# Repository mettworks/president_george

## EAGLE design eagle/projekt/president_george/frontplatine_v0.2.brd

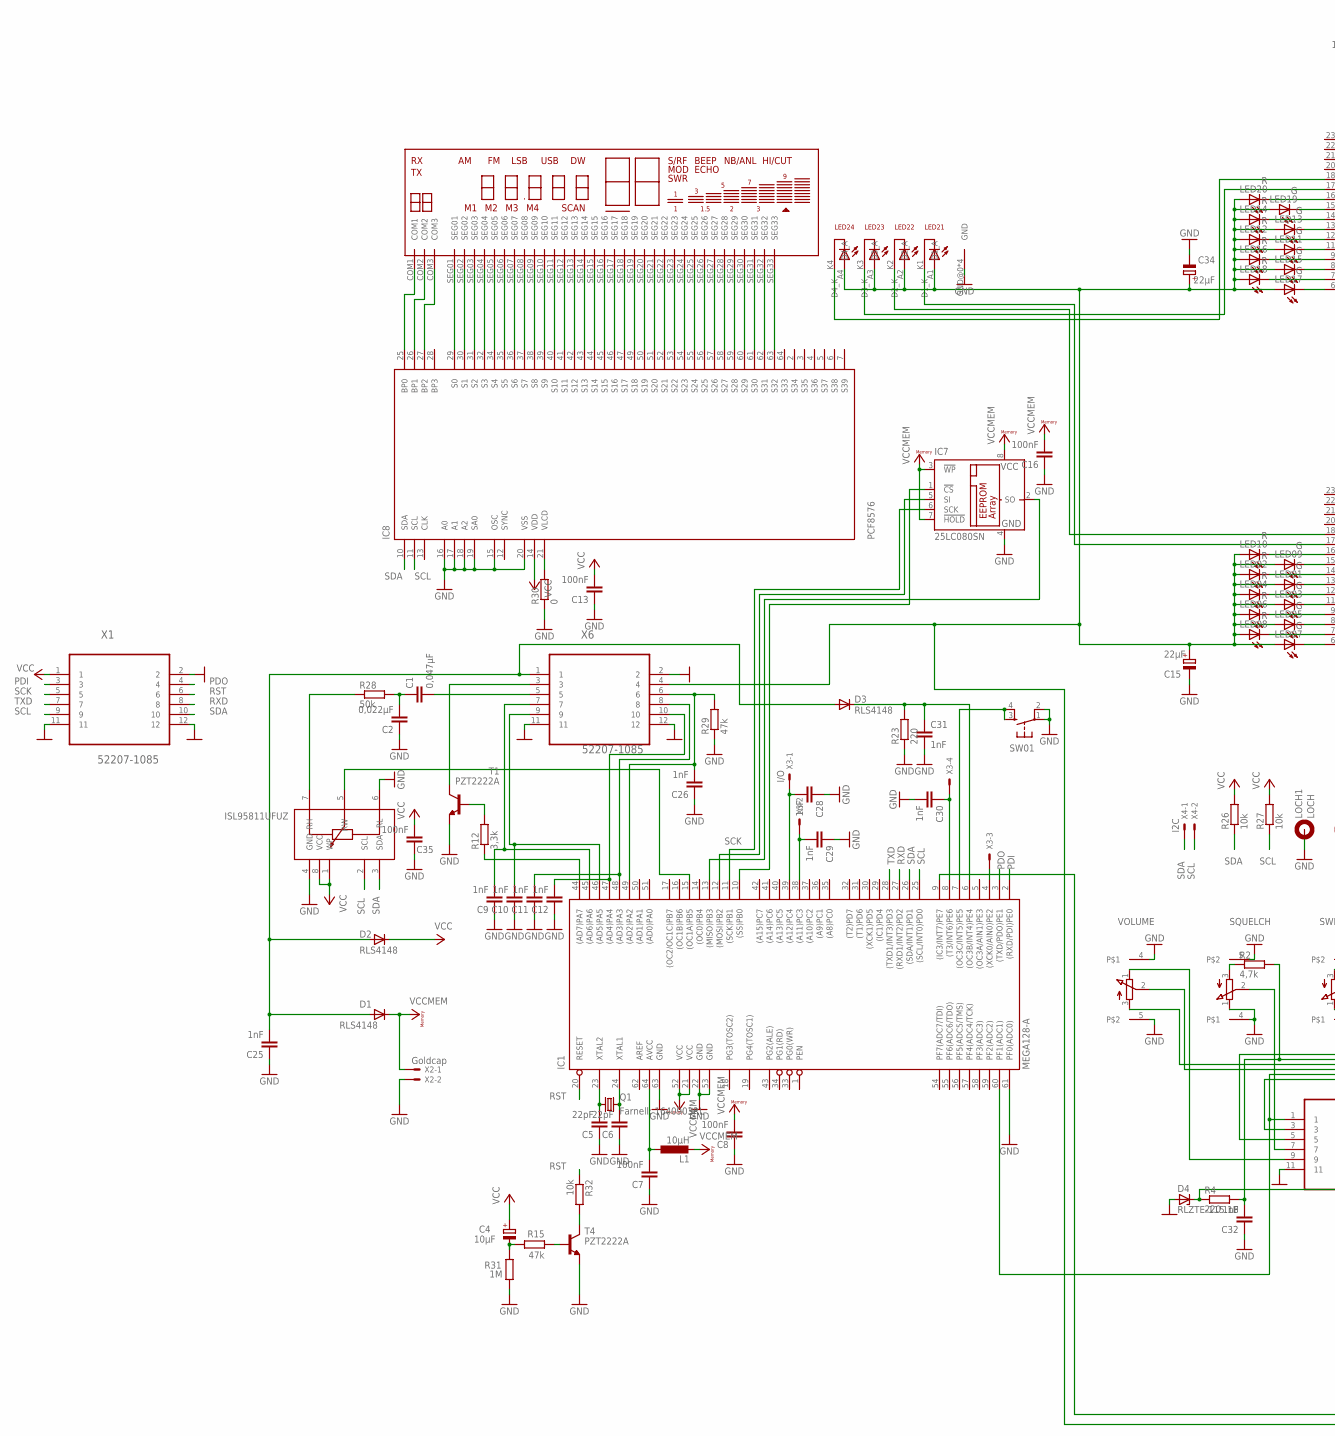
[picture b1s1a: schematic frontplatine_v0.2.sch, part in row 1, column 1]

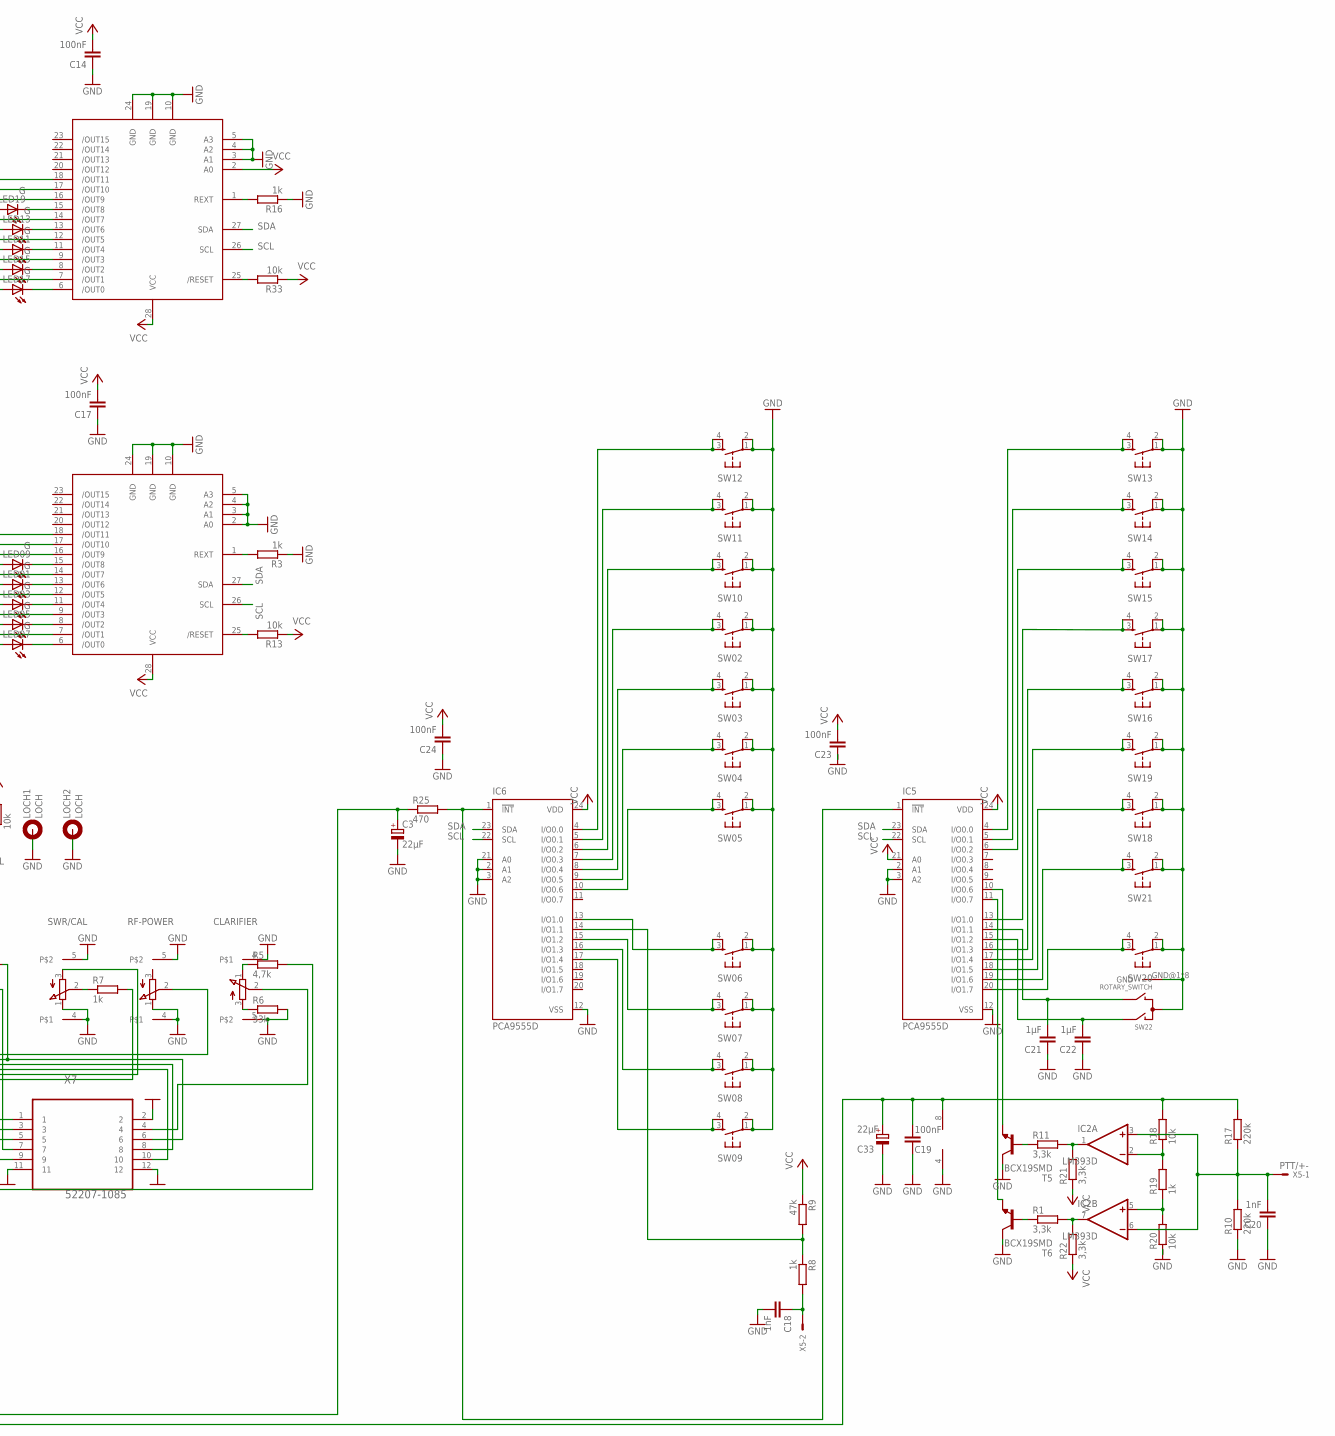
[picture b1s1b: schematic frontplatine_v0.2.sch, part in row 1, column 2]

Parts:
C1: 0,047µF; C1206
C2: 0,022µF; C1206
C3, C15, C33, C34: 22µF; CT3216
C4: 10µF; CT3216
C5, C6: 22pF; C1206
C7, C8, C13, C14, C16, C17, C19, C23, C24, C35: 100nF; C1206
C9, C10, C11, C12, C18, C20, C25, C26, C28, C29, C30, C31, C32: 1nF; C1206
C21, C22: 1µF; C1206
CLARIFIER: POTI
D1, D2, D3: RLS4148; SOD80C
D4: RLZTE-115.1B; SOD80C
DISPLAY1: DISPLAY
IC1: MEGA128-A; TQFP64
IC2: LM393D; SO08
IC3, IC4: TLC59116; TSSOP28
IC5, IC6: PCA9555D; SO24
IC7: 25LC080SN; SO-08; MPN 25LC080/SN
IC8: PCF8576; LQFP-ST-64-2
IC9: ISL95811UFUZ; MSOP8
L1: 10µH; L1812
LED01, LED03, LED05, LED07, LED09, LED11, LED13, LED15, LED17, LED19: G; CHIPLED_1206
LED02, LED04, LED06, LED08, LED10, LED12, LED14, LED16, LED18, LED20: R; CHIPLED_1206
LOCH1, LOCH2: LOCH
Q1: Farnell: 1640903RL; HC49UP
R1, R11, R12, R21, R22: 3,3k; R1206
R2, R5: 4,7k; R1206
R3, R7, R8, R16, R19: 1k; R1206
R4, R23: 220; R1206
R6: 33k; R1206
R9, R15, R29: 47k; R1206
R10, R17: 220k; R1206
R13, R18, R20, R26, R27, R32, R33: 10k; R1206
R25: 470; R1206
R28: 50k; R1206
R30: 0; R1206
R31: 1M; R1206
RF-POWER: POTI
SQUELCH: POTI
SW01, SW02, SW03, SW04, SW05, SW06, SW07, SW08, SW09, SW10, SW11, SW12, SW13, SW14, SW15, SW16, SW17, SW18, SW19, SW20, SW21: TASTER
SW22: ROTARY_SWITCH
SWR/CAL: POTI
T1, T4: PZT2222A; SOT223
T5, T6: BCX19SMD; SOT23-BEC
VOLUME: POTI
X1: 52207-1085; MOLEX_52207-1085
X2: Goldcap; 53047-02
X3: I/O; 53047-04
X4: I2C; 53047-02; MPN 53047-0210
X5: PTT/+-; 53047-02; MPN 53047-0210
X6, X7: 52207-1085; MOLEX_52207-1085; MPN 52207-1085

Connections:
GND: C2.1, C3.-, C5.1, C6.1, C7.1, C8.1, C9.1, C10.1, C11.1, C12.1, C13.1, C14.1, C15.-, C16.1, C17.1, C18.2, C19.1, C20.1, C21.1, C22.1, C23.1, C24.1, C25.1, C26.1, C28.1, C29.1, C30.2, C31.2, C32.1, C33.-, C34.-, C35.1, CLARIFIER.4, CLARIFIER.5, D4.A, DISPLAY1.GND@0 (GND), DISPLAY1.GND@3 (GND), DISPLAY1.GND@6 (GND), DISPLAY1.GND@7 (GND), IC1.22 (GND), IC1.53 (GND), IC1.61 (PF0(ADC0)), IC1.63 (GND), IC2.4 (V-), IC3.2 (A0), IC3.3 (A1), IC3.4 (A2), IC3.5 (A3), IC3.10 (GND), IC3.19 (GND), IC3.24 (GND), IC4.3 (A1), IC4.4 (A2), IC4.5 (A3), IC4.10 (GND), IC4.19 (GND), IC4.24 (GND), IC5.2 (A1), IC5.3 (A2), IC5.12 (VSS), IC6.2 (A1), IC6.3 (A2), IC6.12 (VSS), IC6.21 (A0), IC7.4 (GND), IC8.15 (OSC), IC8.16 (A0), IC8.17 (A1), IC8.18 (A2), IC8.19 (SA0), IC8.20 (VSS), IC9.4 (GND), IC9.6 (RL), LOCH1.B3,0, LOCH2.B3,0, R3.1, R6.2, R10.1, R16.1, R20.1, R23.1, R29.1, R30.1, R31.2, RF-POWER.1 (E), RF-POWER.4, RF-POWER.5, SQUELCH.1 (E), SQUELCH.4, SQUELCH.5, SW01.1, SW01.2, SW02.1, SW02.2, SW03.1, SW03.2, SW04.1, SW04.2, SW05.1, SW05.2, SW06.1, SW06.2, SW07.1, SW07.2, SW08.1, SW08.2, SW09.1, SW09.2, SW10.1, SW10.2, SW11.1, SW11.2, SW12.1, SW12.2, SW13.1, SW13.2, SW14.1, SW14.2, SW15.1, SW15.2, SW16.1, SW16.2, SW17.1, SW17.2, SW18.1, SW18.2, SW19.1, SW19.2, SW20.1, SW20.2, SW21.1, SW21.2, SW22.C, SW22.GND@1 (GND), SW22.GND@2 (GND), SW22.GND@3 (GND), SW22.GND@4 (GND), SW22.GND@5 (GND), SW22.GND@6 (GND), SW22.GND@7 (GND), SW22.GND@8 (GND), SWR/CAL.1 (E), SWR/CAL.4, SWR/CAL.5, T1.3 (E), T4.3 (E), T5.C, T6.C, VOLUME.4, VOLUME.5, X1.2, X1.11, X1.12, X2.2, X6.2, X6.11, X6.12, X7.2, X7.11, X7.12
unnamed: DISPLAY1.SEG01, IC8.29 (S0)
unnamed: VOLUME.2 (S), X7.10
unnamed: VOLUME.1 (E), X7.9
unnamed: VOLUME.3 (A), X7.8
unnamed: D4.C, R4.1, R5.2
unnamed: SQUELCH.2 (S), X7.7
unnamed: R2.1, SQUELCH.3 (A)
unnamed: C32.2, R2.2, R4.2, X7.6
unnamed: CLARIFIER.1 (E), R5.1
unnamed: CLARIFIER.2 (S), X7.4
unnamed: CLARIFIER.3 (A), R6.1
unnamed: IC3.6 (/OUT0), LED07.C
unnamed: R7.2, X7.3
unnamed: R7.1, SWR/CAL.2 (S)
unnamed: DISPLAY1.SEG02, IC8.30 (S1)
unnamed: IC6.14 (I/O1.1), R8.1, R9.2
unnamed: C18.1, R8.2, X5.2
unnamed: IC6.10 (I/O0.6), SW05.3, SW05.4
unnamed: T1.4 (C), X6.3
unnamed: DISPLAY1.SEG03, IC8.31 (S2)
unnamed: DISPLAY1.SEG04, IC8.32 (S3)
unnamed: IC3.7 (/OUT1), LED08.C
unnamed: R12.2, T1.1 (B)
unnamed: C30.1, IC1.8 ((T3/INT6)PE6), X3.4
unnamed: DISPLAY1.SEG05, IC8.34 (S4)
unnamed: C6.2, IC1.24 (XTAL1), Q1.2
unnamed: R32.2, T4.4 (C)
unnamed: DISPLAY1.SEG06, IC8.35 (S5)
unnamed: DISPLAY1.COM1, IC8.25 (BP0)
unnamed: C5.2, IC1.23 (XTAL2), Q1.1
unnamed: IC5.20 (I/O1.7), SW20.3, SW20.4
unnamed: IC3.9 (/OUT3), LED06.C
unnamed: IC3.12 (/OUT5), LED04.C
unnamed: IC3.14 (/OUT7), LED02.C
unnamed: IC3.16 (/OUT9), LED10.C
unnamed: IC4.6 (/OUT0), LED17.C
unnamed: IC3.15 (/OUT8), LED09.C
unnamed: IC3.13 (/OUT6), LED01.C
unnamed: IC3.11 (/OUT4), LED03.C
unnamed: IC3.8 (/OUT2), LED05.C
unnamed: C20.2, IC2.3 (+IN), IC2.6 (-IN), R10.2, R17.1, X5.1
unnamed: IC3.1 (REXT), R3.2
unnamed: IC3.25 (/RESET), R13.2
unnamed: DISPLAY1.COM2, IC8.26 (BP1)
unnamed: IC4.25 (/RESET), R33.2
unnamed: IC4.1 (REXT), R16.2
unnamed: DISPLAY1.COM3, IC8.27 (BP2)
unnamed: IC4.7 (/OUT1), LED18.C
unnamed: C15.+, C19.2, C33.+, C34.+, DISPLAY1.A1 (D1_A), DISPLAY1.A2 (D2_A), DISPLAY1.A3 (D3_A), DISPLAY1.A4 (D4_A), IC2.8 (V+), LED01.A, LED02.A, LED03.A, LED04.A, LED05.A, LED06.A, LED07.A, LED08.A, LED09.A, LED10.A, LED11.A, LED12.A, LED13.A, LED14.A, LED15.A, LED16.A, LED17.A, LED18.A, LED19.A, LED20.A, R17.2, R18.2, X6.4
unnamed: IC4.8 (/OUT2), LED15.C
unnamed: DISPLAY1.SEG07, IC8.36 (S6)
unnamed: DISPLAY1.SEG08, IC8.37 (S7)
unnamed: DISPLAY1.SEG09, IC8.38 (S8)
unnamed: C21.2, IC5.14 (I/O1.1), SW22.B
unnamed: IC1.60 (PF1(ADC1)), SWR/CAL.3 (A), X7.1
unnamed: IC6.9 (I/O0.5), SW04.3, SW04.4
unnamed: IC6.8 (I/O0.4), SW03.3, SW03.4
unnamed: IC6.7 (I/O0.3), SW02.3, SW02.4
unnamed: IC6.6 (I/O0.2), SW10.3, SW10.4
unnamed: IC6.5 (I/O0.1), SW11.3, SW11.4
unnamed: IC6.4 (I/O0.0), SW12.3, SW12.4
unnamed: C22.2, IC5.15 (I/O1.2), SW22.A
unnamed: IC6.15 (I/O1.2), SW07.3, SW07.4
unnamed: IC6.16 (I/O1.3), SW08.3, SW08.4
unnamed: IC6.17 (I/O1.4), SW09.3, SW09.4
unnamed: IC5.4 (I/O0.0), SW13.3, SW13.4
unnamed: IC1.4 ((XCK0/AIN0)PE2), X3.3
unnamed: C28.2, IC1.39 ((A12)PC4), X3.1
unnamed: C29.2, IC1.38 ((A11)PC3), X3.2
unnamed: IC5.19 (I/O1.6), SW21.3, SW21.4
unnamed: IC5.16 (I/O1.3), SW16.3, SW16.4
unnamed: IC5.18 (I/O1.5), SW18.3, SW18.4
unnamed: IC8.21 (VLCD), R30.2
unnamed: IC1.7 ((OC3C/INT5)PE5), SW01.3, SW01.4
unnamed: DISPLAY1.SEG10, IC8.39 (S9)
unnamed: DISPLAY1.SEG11, IC8.40 (S10)
unnamed: DISPLAY1.SEG12, IC8.41 (S11)
unnamed: DISPLAY1.SEG13, IC8.42 (S12)
unnamed: DISPLAY1.SEG14, IC8.43 (S13)
unnamed: DISPLAY1.SEG15, IC8.44 (S14)
unnamed: DISPLAY1.SEG16, IC8.45 (S15)
unnamed: DISPLAY1.SEG17, IC8.46 (S16)
unnamed: DISPLAY1.SEG18, IC8.47 (S17)
unnamed: DISPLAY1.SEG19, IC8.49 (S18)
unnamed: DISPLAY1.SEG20, IC8.50 (S19)
unnamed: DISPLAY1.SEG21, IC8.51 (S20)
unnamed: DISPLAY1.SEG22, IC8.52 (S21)
unnamed: DISPLAY1.SEG23, IC8.53 (S22)
unnamed: DISPLAY1.SEG24, IC8.54 (S23)
unnamed: DISPLAY1.SEG25, IC8.55 (S24)
unnamed: DISPLAY1.SEG26, IC8.56 (S25)
unnamed: DISPLAY1.SEG27, IC8.57 (S26)
unnamed: DISPLAY1.SEG28, IC8.58 (S27)
unnamed: DISPLAY1.SEG29, IC8.59 (S28)
unnamed: DISPLAY1.SEG30, IC8.60 (S29)
unnamed: DISPLAY1.SEG31, IC8.61 (S30)
unnamed: DISPLAY1.SEG32, IC8.62 (S31)
unnamed: DISPLAY1.SEG33, IC8.63 (S32)
unnamed: IC1.44 ((AD7)PA7), R12.1
unnamed: C9.2, IC1.45 ((AD6)PA6), X6.7
unnamed: C10.2, IC1.46 ((AD5)PA5), X6.9
unnamed: C12.2, IC1.47 ((AD4)PA4), X6.10
unnamed: C11.2, IC1.48 ((AD3)PA3), X6.8
unnamed: IC1.15 ((OC1A)PB5), IC9.5 (RW)
unnamed: C26.2, IC1.49 ((AD2)PA2), R29.2, X6.6
unnamed: C3.+, IC1.9 ((IC3/INT7)PE7), R25.1
unnamed: IC4.9 (/OUT3), LED16.C
unnamed: IC1.10 ((SS)PB0), IC7.1 (!CS)
unnamed: IC4.11 (/OUT4), LED11.C
unnamed: C31.1, D3.C, IC1.6 ((OC3B/INT4)PE4), R23.2
unnamed: C25.2, D1.A, D2.A, D3.A, X6.1
unnamed: IC1.13 ((MISO)PB3), IC7.2 (SO)
unnamed: IC1.12 ((MOSI)PB2), IC7.5 (SI)
unnamed: IC2.5 (+IN), R19.1, R20.2
unnamed: IC2.2 (-IN), R18.1, R19.2
unnamed: IC5.17 (I/O1.4), SW19.3, SW19.4
unnamed: IC2.1 (OUT), R11.2, R21.2
unnamed: IC2.7 (OUT), R1.2, R22.2
unnamed: DISPLAY1.K1 (D1_K), IC3.17 (/OUT10)
unnamed: IC5.10 (I/O0.6), T5.E
unnamed: IC5.6 (I/O0.2), SW15.3, SW15.4
unnamed: IC5.11 (I/O0.7), T6.E
unnamed: C1.2, X6.5
unnamed: C1.1, C2.2, R28.2
unnamed: RF-POWER.2 (S), X7.5
unnamed: IC9.7 (RH), R28.1
unnamed: R11.1, T5.B
unnamed: C4.-, R15.2, R31.1
unnamed: R15.1, T4.1 (B)
unnamed: IC6.13 (I/O1.0), SW06.3, SW06.4
unnamed: R1.1, T6.B
unnamed: C7.2, IC1.64 (AVCC), L1.1
unnamed: IC5.5 (I/O0.1), SW14.3, SW14.4
unnamed: IC5.13 (I/O1.0), SW17.3, SW17.4
unnamed: IC5.1 (!INT), IC6.1 (!INT), R25.2
unnamed: IC4.12 (/OUT5), LED12.C
unnamed: IC4.13 (/OUT6), LED13.C
unnamed: IC4.14 (/OUT7), LED14.C
unnamed: IC4.15 (/OUT8), LED19.C
unnamed: IC4.16 (/OUT9), LED20.C
unnamed: DISPLAY1.K2 (D2_K), IC3.18 (/OUT11)
unnamed: DISPLAY1.K3 (D3_K), IC4.17 (/OUT10)
unnamed: DISPLAY1.K4 (D4_K), IC4.18 (/OUT11)
PDI: IC1.2 ((RXD/PDI)PE0), X1.3
PDO: IC1.3 ((TXD/PDO)PE1), X1.4
RST: IC1.20 (RESET), R32.1, X1.6
RXD: IC1.27 ((RXD1/INT2)PD2), X1.8
SCK: IC1.11 ((SCK)PB1), IC7.6 (SCK), X1.5
SCL: IC1.25 ((SCL/INT0)PD0), IC3.26 (SCL), IC4.26 (SCL), IC5.22 (SCL), IC6.22 (SCL), IC8.11 (SCL), IC9.2 (SCL), R27.1, X1.9, X4.2
SDA: IC1.26 ((SDA/INT1)PD1), IC3.27 (SDA), IC4.27 (SDA), IC5.23 (SDA), IC6.23 (SDA), IC8.10 (SDA), IC9.3 (SDA), R26.1, X1.10, X4.1
TXD: IC1.28 ((TXD1/INT3)PD3), X1.7
VCC: C4.+, C13.2, C14.2, C17.2, C23.2, C24.2, C35.2, D2.C, IC3.28 (VCC), IC4.2 (A0), IC4.28 (VCC), IC5.21 (A0), IC5.24 (VDD), IC6.24 (VDD), IC8.14 (VDD), IC9.1 (WP), IC9.8 (VCC), R9.1, R13.1, R21.1, R22.1, R26.2, R27.2, R33.1, X1.1
VCCMEM: C8.2, C16.2, D1.C, IC1.21 (VCC), IC1.52 (VCC), IC7.3 (!WP), IC7.7 (!HOLD), IC7.8 (VCC), L1.2, X2.1

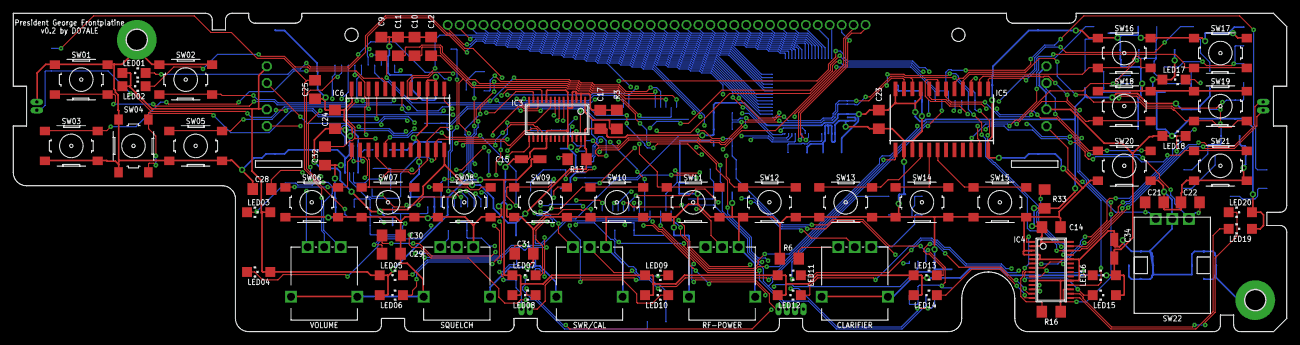
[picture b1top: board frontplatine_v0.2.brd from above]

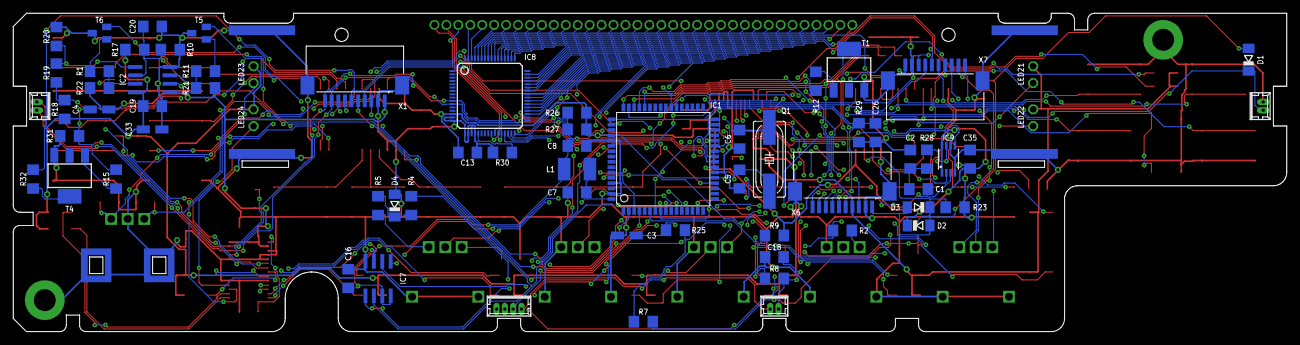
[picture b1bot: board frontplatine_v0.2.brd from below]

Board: 8 copper layers, 192.0 x 48.0 mm, 141 parts (64 on the bottom side), 154 nets.

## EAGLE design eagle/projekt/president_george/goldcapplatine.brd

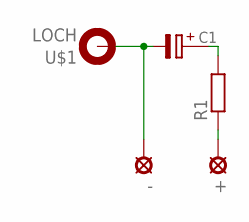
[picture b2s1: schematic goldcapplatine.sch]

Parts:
+: SE11
-: SE11
C1: PAC-21,5; PAC-G-2
R1: R-EU_0207/10; 0207/10
U$1: LOCH

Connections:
unnamed: +.MP, R1.1
unnamed: C1.+, R1.2
unnamed: -.MP, C1.-, U$1.B3,0

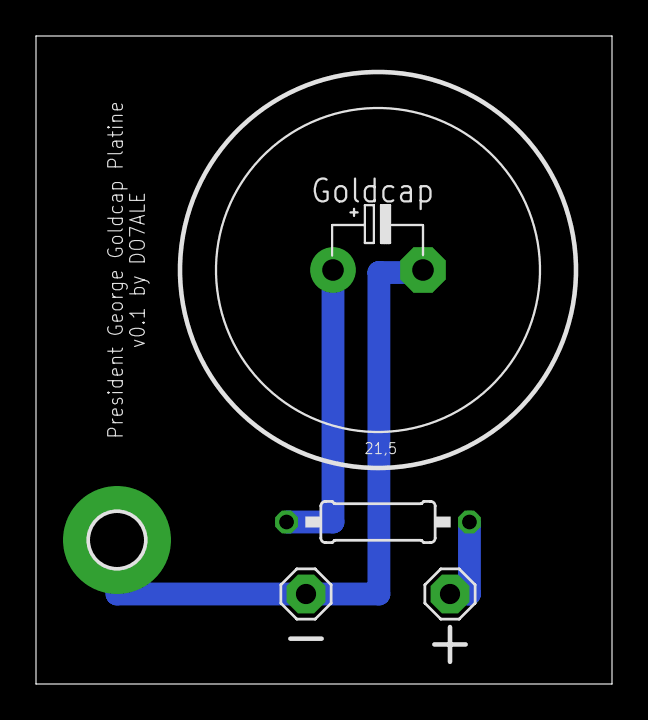
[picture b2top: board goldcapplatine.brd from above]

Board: 8 copper layers, 32.0 x 36.0 mm, 5 parts (0 on the bottom side), 3 nets.

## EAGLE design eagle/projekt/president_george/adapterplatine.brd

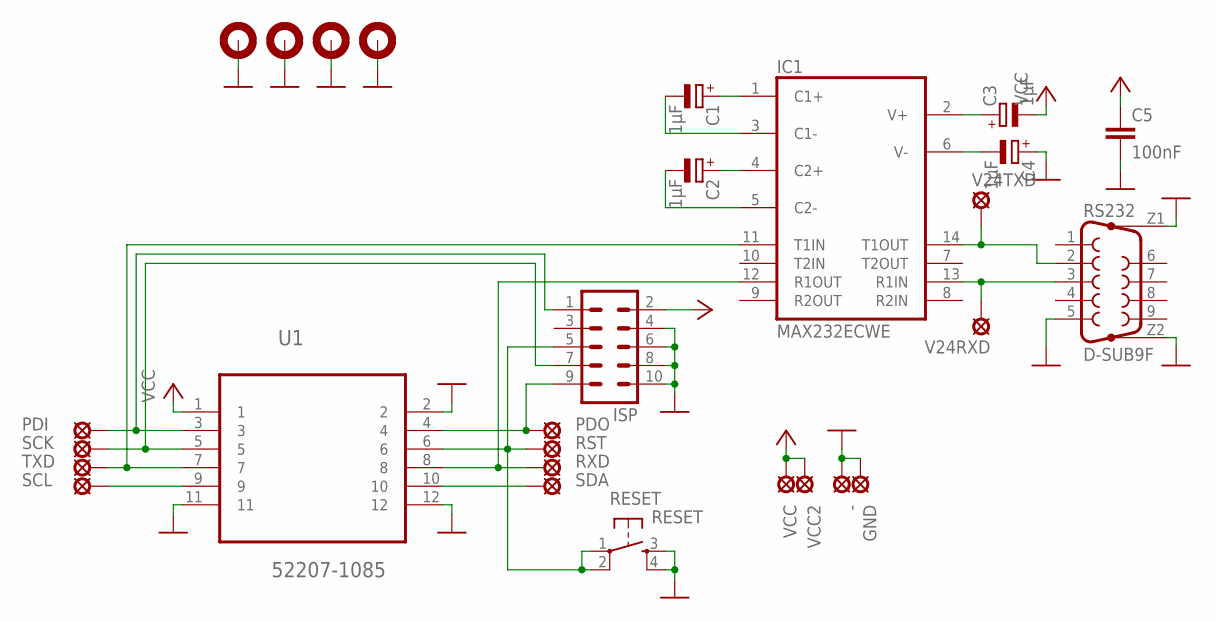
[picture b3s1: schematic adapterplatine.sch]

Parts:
-: SE11
C1, C2, C3, C4: 1µF; CT3216
C5: 100nF; C1206
GND: SE11
IC1: MAX232ECWE; SO16L
ISP: ML10
PDI: SE11
PDO: SE11
RESET: RESET; TASTER
RS232: D-SUB9F
RST: SE11
RXD: SE11
SCK: SE11
SCL: SE11
SDA: SE11
TXD: SE11
U1: 52207-1085; MOLEX_52207-1085
U$1, U$2, U$3, U$4: LOCH
V24RXD, V24TXD: SE11
VCC, VCC2: SE11

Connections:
GND: -.MP, C4.+, C5.2, GND.MP, IC1.15 (GND), ISP.4, ISP.6, ISP.8, ISP.10, RESET.3, RESET.4, RS232.5, RS232.Z1 (G1), RS232.Z2 (G2), U1.2, U1.11, U1.12, U$1.B3,0, U$2.B3,0, U$3.B3,0, U$4.B3,0
unnamed: IC1.14 (T1OUT), RS232.2, V24TXD.MP
unnamed: IC1.13 (R1IN), RS232.3, V24RXD.MP
unnamed: C1.+, IC1.1 (C1+)
unnamed: C1.-, IC1.3 (C1-)
unnamed: C2.+, IC1.4 (C2+)
unnamed: C2.-, IC1.5 (C2-)
unnamed: C4.-, IC1.6 (V-)
unnamed: C3.+, IC1.2 (V+)
unnamed: IC1.11 (T1IN), TXD.MP, U1.7
unnamed: IC1.12 (R1OUT), RXD.MP, U1.8
unnamed: ISP.1, PDI.MP, U1.3
unnamed: ISP.5, RESET.1, RESET.2, RST.MP, U1.6
unnamed: ISP.7, SCK.MP, U1.5
unnamed: ISP.9, PDO.MP, U1.4
unnamed: SCL.MP, U1.9
unnamed: SDA.MP, U1.10
VCC: C3.-, C5.1, IC1.16 (VCC), ISP.2, U1.1, VCC.MP, VCC2.MP

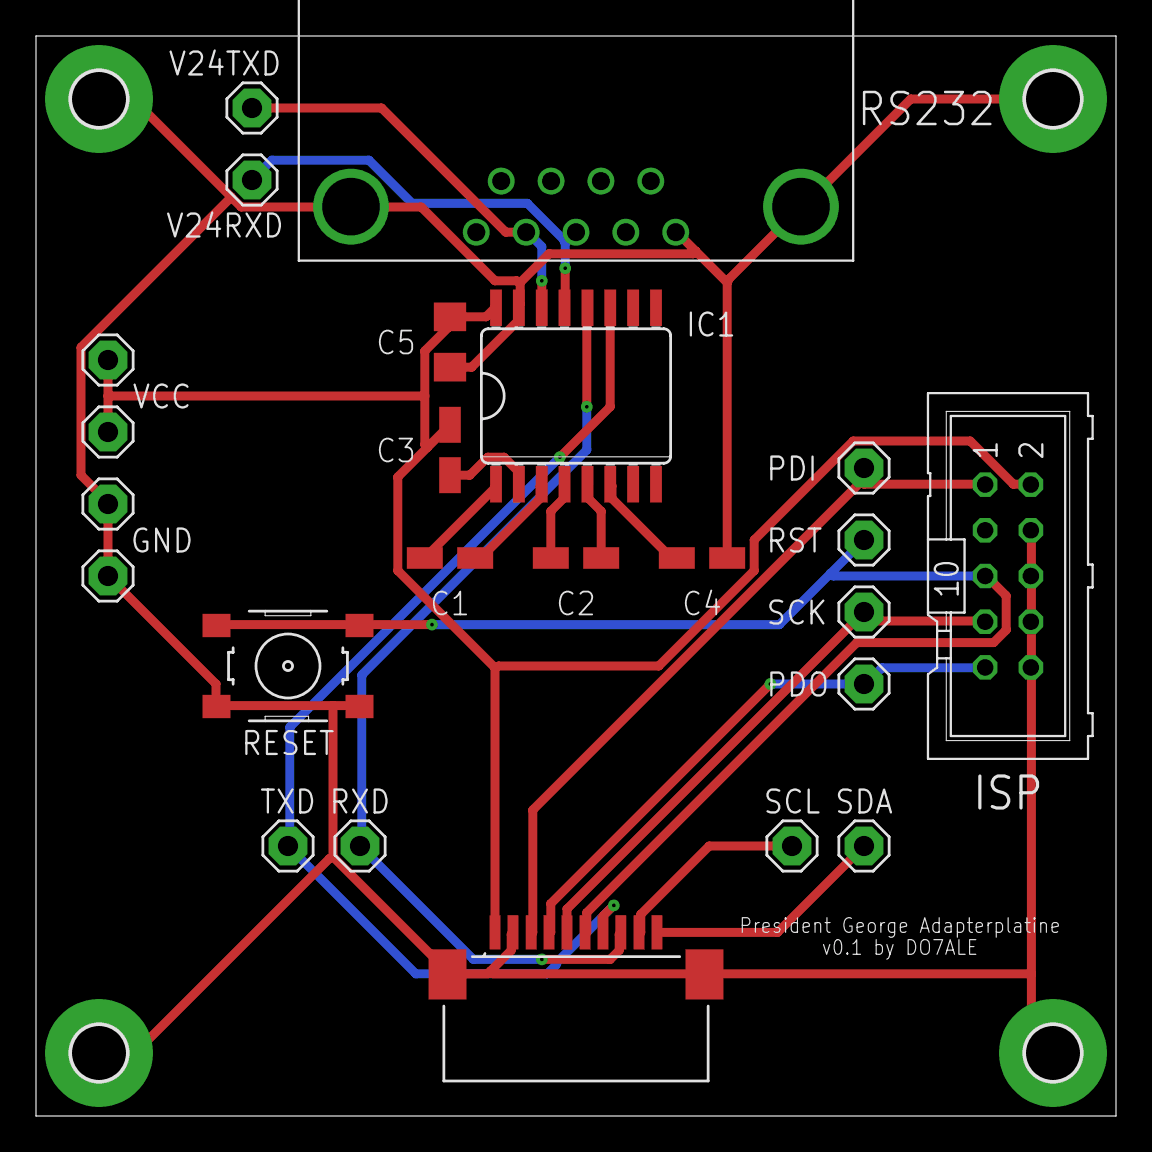
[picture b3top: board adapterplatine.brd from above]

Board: 8 copper layers, 60.0 x 60.0 mm, 28 parts (0 on the bottom side), 18 nets.

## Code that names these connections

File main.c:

/*
avrdude -p atmega128 -P /dev/ttyACM0 -c stk500v2 -v -Uefuse:w:0xFF:m -U hfuse:w:0xC9:m -U lfuse:w:0xDF:m
*/

#include <avr/io.h>
#include <util/delay.h>
#include <avr/interrupt.h>
#include "memory.h"
#include "display.h"
#include "led.h"
#include "transceiver.h"
#include "operating.h"
#include "i2c.h"
#ifdef debug
#include "debug.h"
#include <stdlib.h>
#include <stdio.h>
#include <stdint.h>
#endif

int ichbinaus=0;
int led_farbe=0;
unsigned int led_dimm1=128;
unsigned int led_dimm2=128;
unsigned int memory[MEM_SIZE];
int mod;
//unsigned int freq = 28225;
unsigned int freq;
unsigned int cb_channel;
unsigned int cb_mod;
unsigned int step = 5;
int txstat=0;

int modus;

//
// Counter für S-Meter
unsigned int adccounter=20;
unsigned int adcvalues[20];
#define ADCMESSUNGEN 20;



//
// IRQ für Spannungsabfall
// wegspeichern der Einstellungen im EEPROM
// beim wiederkommen von VCC, wird durch ein RC Glied Reset ausgelöst
ISR (INT4_vect)
{
	#ifdef debug
	uart_puts("INT4_vect()\r\n");
	#endif
	off();
}

ISR (INT5_vect)
{
	#ifdef debug
	uart_puts("INT5_vect()\r\n");
	#endif
	if(ichbinaus == 1)
	{
		#ifdef debug
		uart_puts("AN\r\n");
		#endif
	  PORTA |= (1<<PA7);	// einschalten
		led_pwm(1,0);
		led_pwm(2,0);
		led_pwm(3,0);
		led_pwm(4,0);
		led_pwm(5,0);
		led_pwm(6,0);
		led_pwm(7,0);
		led_pwm(8,0);
		led_pwm(9,0);
		led_pwm(10,0);
		led_pwm(11,0);
		led_pwm(12,0);
		init_geraet();
		ichbinaus=0;
	}
	else
	{
		ichbinaus=1;
		#ifdef debug
		uart_puts("AUS\r\n");
		#endif
		save2memory();
		PORTA &= ~(1<<PA7);	// ausschalten...
		led_pwm(1,0);
		led_pwm(2,0);
		led_pwm(3,0);
		led_pwm(4,0);
		led_pwm(5,0);
		led_pwm(6,0);
		led_pwm(7,0);
		led_pwm(8,0);
		led_pwm(9,0);
		led_pwm(10,0);
		led_pwm(11,0);
		led_pwm(12,0);
	}
}

ISR (INT7_vect)
{
	
	#ifdef debug
	uart_puts("INT7\r\n");
	#endif
	
	keycheck();
}



ISR(BADISR_vect)
{
	#ifdef debug
  uart_puts("RESET AUSGELOEST!\r\n");
	uart_puts("nicht definierter Interrupt!\r\n");
	uart_puts("STOP\r\n");
	#endif
	while(1)
	{
	}
}
/*
//
// sehr unelegant, muss mit einem Timer gemacht werden
// erstmal geht es nur um den HW Test ... ^^
void scan(void)
{
	while(1)
	{
		freq=freq+step;
		tune(freq,step);
		_delay_ms(250);
		if ( !(PINA & (1<<PINA2)) )
		{
			#ifdef debug
			uart_puts("Treffer\r\n");
			#endif
			break;
		}
	}
}
*/

uint16_t adc_read(void )
{
	// ADC1 auswählen
	//ADMUX |= (1<<MUX0);
	//ADMUX |= (1 << MUX3) | (1<<MUX0);
	ADMUX |= (1<<MUX0);

  ADCSRA |= (1<<ADSC);
  while (ADCSRA & (1<<ADSC) ) 
	{   
  }
  return ADCW;                   
}

void messung_s(void)
{
	uint16_t messwert;
	messwert=adc_read();
	uint32_t sum=0;
	unsigned int i;
	//char s[7];

	
	if(adccounter == 0)
	{
		i=ADCMESSUNGEN;
		while(i > 0)
		{
			sum=sum+adcvalues[i];
			i--;
		}
		sum=sum/ADCMESSUNGEN;
		/*
		uart_puts("Durchschnitt: ");
		uart_puts( itoa( sum, s, 10 ) );
		uart_puts("\r\n");
		*/
		display_write_meter(sum);
		adccounter=ADCMESSUNGEN;
	}
	else
	{
		adcvalues[adccounter]=messwert;
		adccounter--;
	}
}


void adc_init(void)
{
	ADCSRA |= (1 << ADPS2) | (1 << ADPS1) | (1 << ADPS0); // Set ADC prescaler to 128 - 125KHz sample rate @ 16MHz
	ADMUX |= (1 << REFS0) | (1 << REFS1); 	// 2.65 V

	ADCSRA |= (1 << ADEN);  // Enable ADC
	ADCSRA |= (1 << ADSC);  // Start A2D Conversions	
}

ISR (TIMER0_COMP_vect)
{
	#ifdef debug
	uart_puts("INT Timer0\r\n");
	#endif
	keycheck();
}


ISR (TIMER1_COMPA_vect) 
{
	#ifdef debug
	uart_puts("INT Timer1\r\n");
	#endif
  PORTB ^= (1 << 5);
}

void init_timer0(void)
{
	//
	// http://timogruss.de/2013/06/die-timer-des-atmega128-ctc-modus-clear-timer-on-compare/
	// das ist Timer0
	// Register TIMSK, Bit OCIE0 startet den INT
	TCCR0 |= (1 << WGM01)|(1 << CS02)|(1 << CS00);
	TCNT0 = 0x00; //Timer 0 mit Null initialisieren
	OCR0 = 255;  //Vergleichsregister initialisieren
}

void init_timer1(void)
{
	// 
	// Anregung: http://www.mikrocontroller.net/topic/215420
	DDRB |= (1<<PB5); 
	
	TCCR1A |= (1 << WGM11) | (1<<COM1A1);
	// 64 ist Vorteiler
	TCCR1B |= (1 << WGM13) | (1 << WGM12) | (1 << CS10) | (1 << CS11);

	ICR1 = (((18432000/64) / 100) - 1); //TOP
	OCR1A = (((18432000/64) / 100) - 1)/2;
}

void set_timer0(char status)
{
	if(status == 0)
	{
		#ifdef debug
		uart_puts("Timer0 gestoppt\r\n");
		#endif
		TIMSK &= ~(1 << OCIE0);
	}
	else
	{
		#ifdef debug
		uart_puts("Timer0 gestartet\r\n");
		#endif
		TIMSK |= (1 << OCIE0);
	}
}

void set_timer1(char status)
{
	/*
	if(status == 0)
	{
		#ifdef debug
		uart_puts("Timer1 gestoppt\r\n");
		#endif
		TIMSK &= ~(1 << OCIE1A);
	}
	else
	{
		#ifdef debug
		uart_puts("Timer1 gestartet\r\n");
		#endif
		TIMSK |= (1 << OCIE1A);
	}
	*/
}

int main(void) 
{
	//cli();
  #ifdef debug
	inituart();
  uart_puts("\r\n\r\n");
	uart_puts("Beginn main()\r\n");
	#endif
	_delay_ms(1000);
  //
  // Ein und Ausgaenge
	// PE4, INT4 ist VCC Kontrolle					-> Eingang
	// PE7, INT7 ist 1. Port Expander				-> Eingang
	// PE6, INT6 ist 2. Port Expander				-> Eingang
 	// PE5, INT5 ist Taster 1, Ein/Aus			-> Eingang
  // PA4 ist Latch PLL      							-> Ausgang		PIN10 vom Mainboard     
  // PA6 ist Latch Treiber  							-> Ausgang		PIN7 vom Mainboard     
  // PA5 ist Data	    										-> Ausgang		PIN9 vom Mainboard   
  // PA3 ist Clock	    									-> Ausgang		PIN8 vom Mainboard     
	// PC0 ist LED Rot											-> Ausgang
	// PC1 ist LED Grün 										-> Ausgang
	// PA7 ist Ein/Aus											-> Ausgang
	// PA2 ist "Busy" (Rauschsperre offen)	-> Eingang
	
	// PE4
	DDRE &= ~(1<<PE4);	// Eingang
	// PE7
	DDRE &= ~(1<<PE7);	// Eingang
  PORTE |= (1<<PE7);	// internen Pullup aktivieren
	// PE6
	DDRE &= ~(1<<PE6);	// Eingang
  PORTE |= (1<<PE6);	// internen Pullup aktivieren
	// PE5
  DDRE &= ~(1<<PE5);	// Eingang
  PORTE |= (1<<PE5);	// internen Pullup aktivieren

	// PC0
	DDRC |= (1<<PC0);
	// PC1
	DDRC |= (1<<PC1);
	// PA7
	DDRA |= (1<<PA7);
  PORTA |= (1<<PA7);	// einschalten
	// PA2
	DDRA &= ~(1<<PA2);	// Eingang
	
	//
	// Interrupts
	// INT4 wird bei fallender Flanke ausgelöst -> VCC weg
	// INT7 wird für den 1. i2c Port Expander genutzt
	// (warum nicht bei fallender Flanke? Hmmm!)
	
	EICRB |= (0 << ISC70) | (0 << ISC71);    // 0 löst aus
	EICRB |= (0 << ISC60) | (0 << ISC61);    // 0 löst aus
  EICRB |= (0 << ISC40) | (1 << ISC41);    // fallende Flanke
	EICRB |= (0 << ISC50) | (1 << ISC51);    // fallende Flanke
	EIMSK |= (1 << INT4) | (1<< INT7) | (1<< INT5) | (1<< INT6);
	

	
	mod=1;
	i2c_init();
	init_geraet();
	display_init();
	init_led();
	led_helligkeit1(led_dimm1);
	led_helligkeit2(led_dimm2);
	led_color(led_farbe);
	display_write_modus(0);
	//adc_init();

	init_timer0();
	init_timer1();
	//set_timer1(1);
	
	sei();

	while(1)
	{
		//messung_s();
	}
} 

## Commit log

2012-11-18 first
2012-11-18 - Initial
2012-11-27 - es tut was... :-)
2012-11-28 - aufgeraeumt - PLL Init kommentiert und richtig gemacht (Verstanden... :-) ) - Treiberbaustein wird richtig angesprochen
2013-02-25 - tune Funktion eingebaut - Code bereinigt
2013-03-10 - TX/RX Erkennung - Einschalten per �C (noch ohne Taster)
2013-03-12 - 4 Taster: Down, Up, Modulation, Step - Funktionen der Taster eingebaut - debug Meldungen verbessert - Treiberansteuerung nun mit Bitmanipulation
    Wird langsam ein richtiges Funkger�t... :-)
2013-03-12 - Fehler berichtigt
2013-03-14 - Testweise i2c fuer ein Digital Poti (AD5241) eingebaut (soll fuer die LED Helligkeit genutzt werden) - die Pin's fuer den 3 Leiter Bus sind umgezogen um Platz fuer den i2c Bus zu machen
2013-03-16 - der Atmega8 wurde durch einen Atmega128 ersetzt
2013-03-19 - testweiser Einbau vom PCF8576 - Ansteurung per i2c erfolgreich
2013-03-27 - weitere Tests mit PCF8576, arbeitet immer noch nicht recht mit 3 BP's ... :-(
2013-05-01 LED Treiber
    - LED Treiber
    - jetzt wird winavr genutzt...
2013-05-01 LED, Farbumschaltung
2013-05-26 Prototyp wieder komplett verkabelt
2013-05-28 TODO-Liste hinzugefügt
2013-05-28 TODO
2013-06-03 IRQ fuer Spannungswegfall
    - wenn VCC weg ist, wird INT4 ausgelöst
    - Vorbereitung für Speicherfunktion
    - Wechsel auf Goldcap...
    - es fehlt noch Reset wenn VCC wieder da ist...
2013-06-04 1. Versuch SPI EEPROM
    - nicht funktional !
2013-06-05 SPI EEPROM funktioniert
    - 25LC1024
    - Testbyte schreiben und lesen funktioniert
    - der Schreibvorgang dauerte mit 8ms unerwartet lange... (wer lesen
    kann...)
    Anregung von http://www.mikrocontroller.net/topic/260261
2013-06-06 Typo & Bug
    - Typo eliminiert
    - Bug eingebaut :-(
2013-06-06 Bugsuche...
    - kapott
2013-06-06 EEPROM wird richtig beschrieben
    - weiter testen
2013-06-06 aufgeräumt
2013-06-06 Debugmeldungen bei EEPROM lesen und schreiben
2013-06-10 Anpassungen laut Schaltplan
    - Schaltplan und Quellcode synchronisiert
    - i2c erstmal auskommentiert
    - Testen der Komparatoren fuer Up/Down vom Mikro -> Gerät muss
    eingeschaltet sein
2013-07-10 PCA9555D
    - 1. Byte auslesen ok
2013-07-10 PCA9555D und INT
    geht noch nicht per INT... :-(
2013-08-02 Speichern im EEPROM
    - die letzte Frequenz wird nun im EEPROM abgespeichert
2013-08-02 Bugfixing
    - wenn eine Taste zuoft gedrückt wurde, hatte sich der AVR zurückgesetzt
    -> Interrupts und i2c passt nicht zusammen -> behoben
    - aufgeräumt
2013-08-03 Ausschalten, Aufgeräumt
    - abschalten, mit extra Taster
    - Ein und Ausgänge entrümpelt
2013-08-03 2. Port Expander
    - 2. Port Expander eingesetzt -> 2. INT Verarbeitung
2013-08-05 1. Versuch, mehrere Tastendrücke abfangen
    Wenn Taster gedrückt, wird Status abgeholt und danach Timer0 gestartet
    um längere Tastendrücke abzufangen.
2013-08-05 Tastenverarbeitung fertig
    - Interrupts für Tasten
    - mehrfache Tastendrücke werden erkannt
    - PTT läuft
    - aufgeräumt
2013-08-06 Roger Beep eingebaut
2013-08-06 einfache Scan Funktion
    - sehr rudimentär!
2013-08-06 ADC Messung, Bullshit
    Hmmm...
2013-08-06 ADC 2. Versuch
    Hmmm...
2013-08-07 ADC arbeitet
    - interne VREF 2,65V
    - alternativ noch 10x Gain (ADC1 Signal, ADC0 GND)
    - muss dann mal mit einem Messender angepasst werden... :-)
2013-08-09 Interrupts verbessert
    INT6 und 7 (die Expander) lösen jetzt nur bei 0 aus, dadurch gibt es
    keine/geringe Probleme mehr bei Einstrahlungen.
2013-08-13 Debug raus
    endif usw. eingebaut
2013-08-13 SPI Optimierung, Bugfix
    - Timing vom SPI verbessert
    - Bug gefunden der bei abgeschalteten Debugging zu einem stummen Gerät
    führte... ;-)
2013-08-14 Endstufe nun OK
    Endstufe wurde nicht richtig angesteuert, nun wird auch mit voller
    Leistung gesendet.
    unschöner Code vom testen...
2013-08-14 Kapott
    Senden geht wieder nicht... Morgen ist auch noch ein Tag...
2013-08-14 Test Endstufe
    Vermutlich behindern INTERRUPT Auslösungen die SPI Übertragungen...
2013-08-17 Test Endstufe
    immer noch keine Leistung... :-(
2013-08-27 Funktionsfähig
    - Endstufe scheint defekt zu sein (2. Gerät getestet)
    weiter im Programm
2013-08-27 Kleinkram
2013-09-01 Version 0.1
    - Display wird nur testweise angesteuert
    - HW arbeitet nun komplett
2013-09-01 Test ADC
    - ADC musste noch getestet werden...
2013-09-24 Display begonnen
    - Display Funktion begonnen
    - Ufff...
2013-09-28 Display
    Noch am überlegen und testen...
2013-09-29 Display
    1. Version die Sinn macht
2013-09-29 Display
    Testweise im 4 BP Betrieb, funktioniert.
    Seltsame Probleme...
2013-09-30 Display
    - noch ein Versuch mit 3 BP's
    - einzelne Bits gehen nicht... :-(
2013-09-30 Display
    - sieht besser aus...
    - besseres Datenblatt verschafft Klarheit
2013-10-14 Display
    - Kanalanzeige arbeitet
2013-10-15 Display
    - Frequenzanzeige
    - Modulationsanzeige
    - TX/RX
2013-10-21 Prototyp v0.1 Aufbau
    - Taster
    - LED's
2013-10-27 Prototyp v0.1 Aufbaue
    - Tests
    - TODO angepasst
2013-10-28 Prototyp v0.1 Aufbau
    - Display wieder umgebaut ...
    - Tasten angepasst
    - Tests
2013-11-19 Prototyp v0.1 Aufbau
    - aufräumen des Codes
    - unterteilung in Einzeldateien
    - Warnings eliminieren
    BUG!
2013-11-21 Code bereinigt
    - Header Dateien angelegt
    - debug und Oszillator frequenz nun im Makefile festgelegt
    - keine Warnings mehr! :-)
2013-11-21 Prototyp v0.1 Aufbau
    - Tastendrücke kommen jetzt besser an
    - vermutlich schwingt der OP für die Mikrofontasten...
2013-11-23 Prototyp v0.1 Aufbau
    - TX/RX Umschaltung
    - Kleinkram
2013-11-23 Prototyp v0.1 Aufbau
    - Abspeichern Frequenz und Modulation eingebaut
    - Debug Meldungen aufgeräumt
    :-)
2013-11-24 Prototyp v0.1 Aufbau
    - feste Frequenz vom testen vergessen...
2013-11-24 Prototyp v0.1 Aufbau
    - speichern im EEPROM verbessert
    - Modusumschaltung zwischen HAM und CB
    CB Modus nur Empfang!
2013-11-25 Prototyp v0.1 Aufbau
    - ADC für das S-Meter eingebaut
    Der IRQ für VCC Wegfall geht nicht mehr... ? Die anderen schon... ?
2013-11-26 Prototyp v0.1 Aufbau
    - Fehlersuche
    An den Display Controller schreiben verhindert den abschalten IRQ... ?
2013-11-29 Prototyp v0.1 Aufbau
    - ADC geht nicht per INT, ist wohl zuviel
    - ADC per while klappt einwandfrei
2013-11-30 Prototyp v0.1 Aufbau
    - Bugfix, Crash on tuning
2013-12-02 Prototyp v0.1 Aufbau
    - first version with CTCSS
2013-12-05 Prototyp v0.1 Aufbau
    - Fehlersuche
2013-12-12 Prototyp v0.1 Aufbau
    - playing with Timers
    - Debugswitch completed
2013-12-13 Prototyp v0.1 Aufbau
    - playing with PWM for CTCSS Tones, works :-)
2013-12-15 Prototyp v0.1 Aufbau
    - Switch for CTCSS Tone (now hardcoded), Relais (-100kHz), Echo,
    Rogerbeep (2 Tone Beep... ^^)
    - Transceiver doesn't work on 29690 ... :-|
2013-12-31 TEST
2014-01-01 - better handling with the cb channels (now I'm back to linux...)
2014-02-03 - Directory Structure
2014-02-03 - added the eagle stuff
2014-02-03 - checking the brd files
2014-02-03 - deleted wrong netclass von frontplatine
2014-02-03 - Shopping List upgraded
2014-03-01 - test
2014-03-02 - v0.2 Aufbau
2014-03-02 v0.2 Aufbau
2014-03-03 - LED switching working - Hi Power Mode activated... 8-)
2014-03-08 - optimized switching beetween ham and cb - cleaning - on the new pcb layout uses the keys different input pins on the port expander, fixed
2014-03-12 - searching bug :-|
2014-03-13 - Function Key is working
2014-03-16 - added support VFO A and B - freq is now unsigned long
2014-03-17 - VFO A/B now working - M1 + SELECT clears the memory and reset the device
2014-03-18 - saving the modulation for vfo a and b - byte/bit voodoo... :-)
2014-03-24 - playing with the keys - fixed gcc warnings
2014-03-24 - fixed min max values for frequencies
2014-03-26 - fixed tune() - memory reading/writing changed to new system
2014-03-27 - strange problem with timer and f key ?? - implemented switching between steps - implemented split function
2014-03-27 - on/off
2014-04-04 - Bugfix, Split Mode now working
2014-04-04 - Things
2014-05-26 - Fixed RB - TODO: no low frequencies!
2014-05-26 - played with keys
2014-05-27 - Haha
2014-05-27 - Memory Saving Settings
2014-06-02 - cleanup - fixed speed for dialknob
2014-06-29 - Fixed Timer for F Key
2014-06-30 - Timer3 is very strange!
2014-07-02 - Timer3 now works as expected
2014-07-07 - fixed LSB (-5kHz) - many changes, because display freq and so on - fixed CB Mode
2014-07-08 - Bugfix
2014-08-10 - Bugfixes - LED Color and Brightness prepared for storing - strange saving problems...
2014-08-11 - Bugfixes... HTH...
2015-12-08 - fixed s-meter (harhar, shitty hardware...) - testing 12m, receiving works...
2015-12-08 - removed old variables
2015-12-14 - i2c poti
